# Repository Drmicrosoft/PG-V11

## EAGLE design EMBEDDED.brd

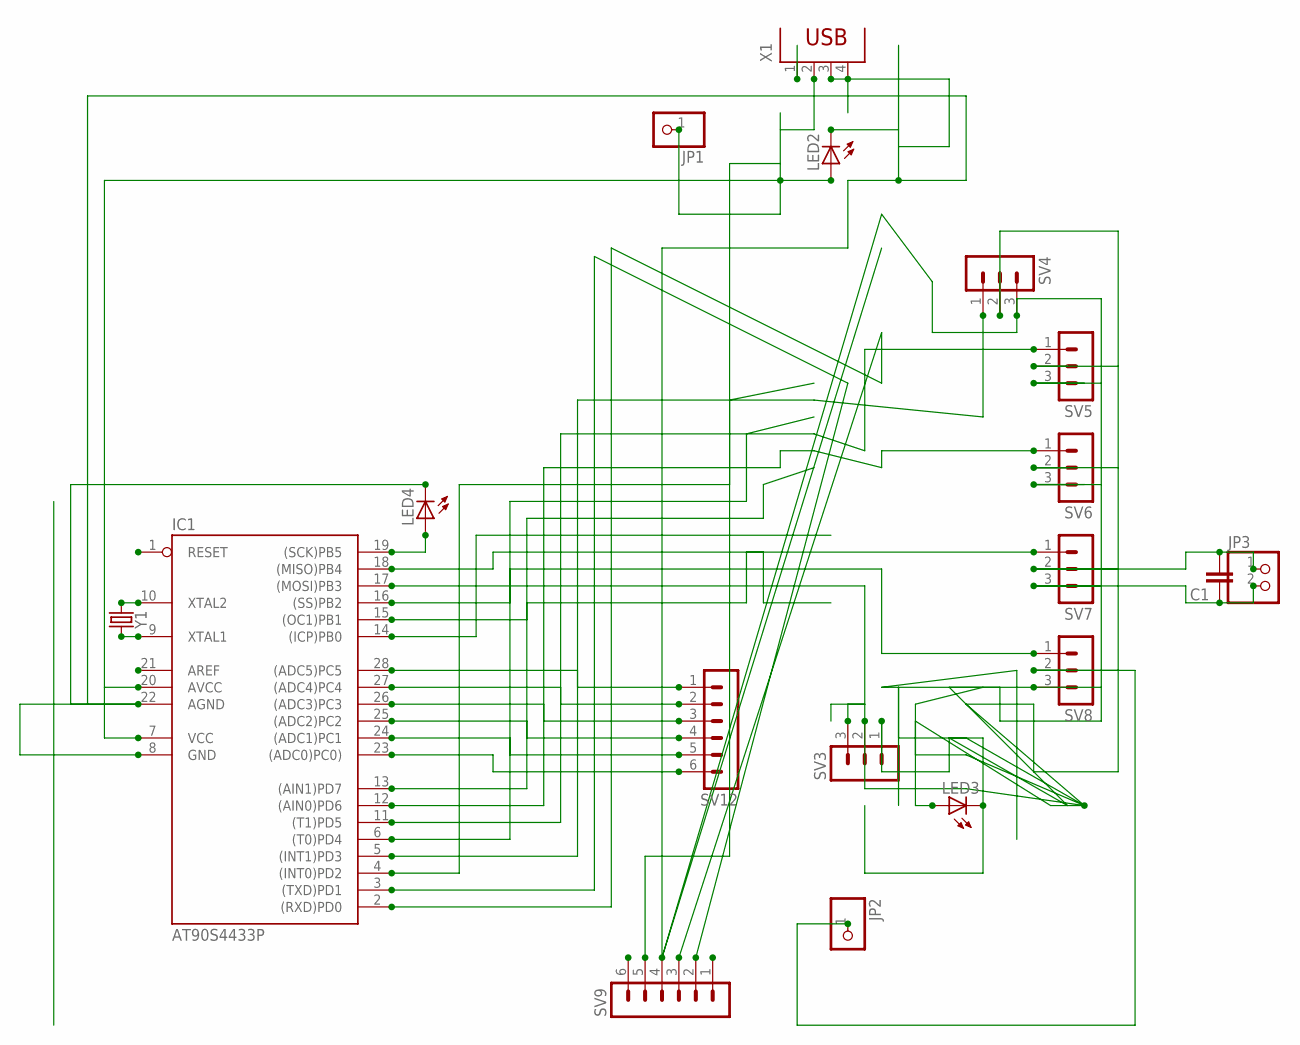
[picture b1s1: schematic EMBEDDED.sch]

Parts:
C1: C5/2.5; C5B2.5
IC1: AT90S4433P; DIL28-3
JP1, JP2: PINHD-1X1; 1X01
JP3: PINHD-1X2; 1X02
LED2, LED3, LED4: LEDLD260; LD260
SV3, SV4, SV5, SV6, SV7, SV8: MA03-1
SV9, SV12: MA06-1
X1: PN61729
Y1: CRYSTALPTH-HC49US; HC49US

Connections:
GROUND: C1.1, IC1.8 (GND), IC1.22 (AGND), JP3.2, LED2.K (C), LED3.K (C), LED4.K (C), SV3.1, SV4.3, SV5.3, SV6.3, SV7.3, SV8.3, SV9.4, X1.3
unnamed: IC1.17 ((MOSI)PB3), SV3.3
unnamed: C1.2, JP2.1, JP3.1, LED3.A, SV3.2, SV4.2, SV5.2, SV6.2, SV7.2, SV8.2
unnamed: IC1.16 ((SS)PB2), SV8.1
unnamed: IC1.15 ((OC1)PB1), SV7.1
unnamed: IC1.12 ((AIN0)PD6), SV6.1
unnamed: IC1.28 ((ADC5)PC5), SV12.1
unnamed: IC1.11 ((T1)PD5), SV5.1
unnamed: IC1.9 (XTAL1), Y1.2
unnamed: IC1.5 ((INT1)PD3), SV4.1
unnamed: IC1.27 ((ADC4)PC4), SV12.2
unnamed: IC1.26 ((ADC3)PC3), SV12.3
unnamed: IC1.2 ((RXD)PD0), SV9.3
unnamed: IC1.3 ((TXD)PD1), SV9.2
unnamed: IC1.25 ((ADC2)PC2), SV12.4
unnamed: IC1.24 ((ADC1)PC1), SV12.5
unnamed: IC1.23 ((ADC0)PC0)), SV12.6
unnamed: IC1.10 (XTAL2), Y1.1
unnamed: IC1.19 ((SCK)PB5), LED4.A
VOLTAGE: IC1.7 (VCC), IC1.20 (AVCC), JP1.1, LED2.A, SV9.5, X1.2

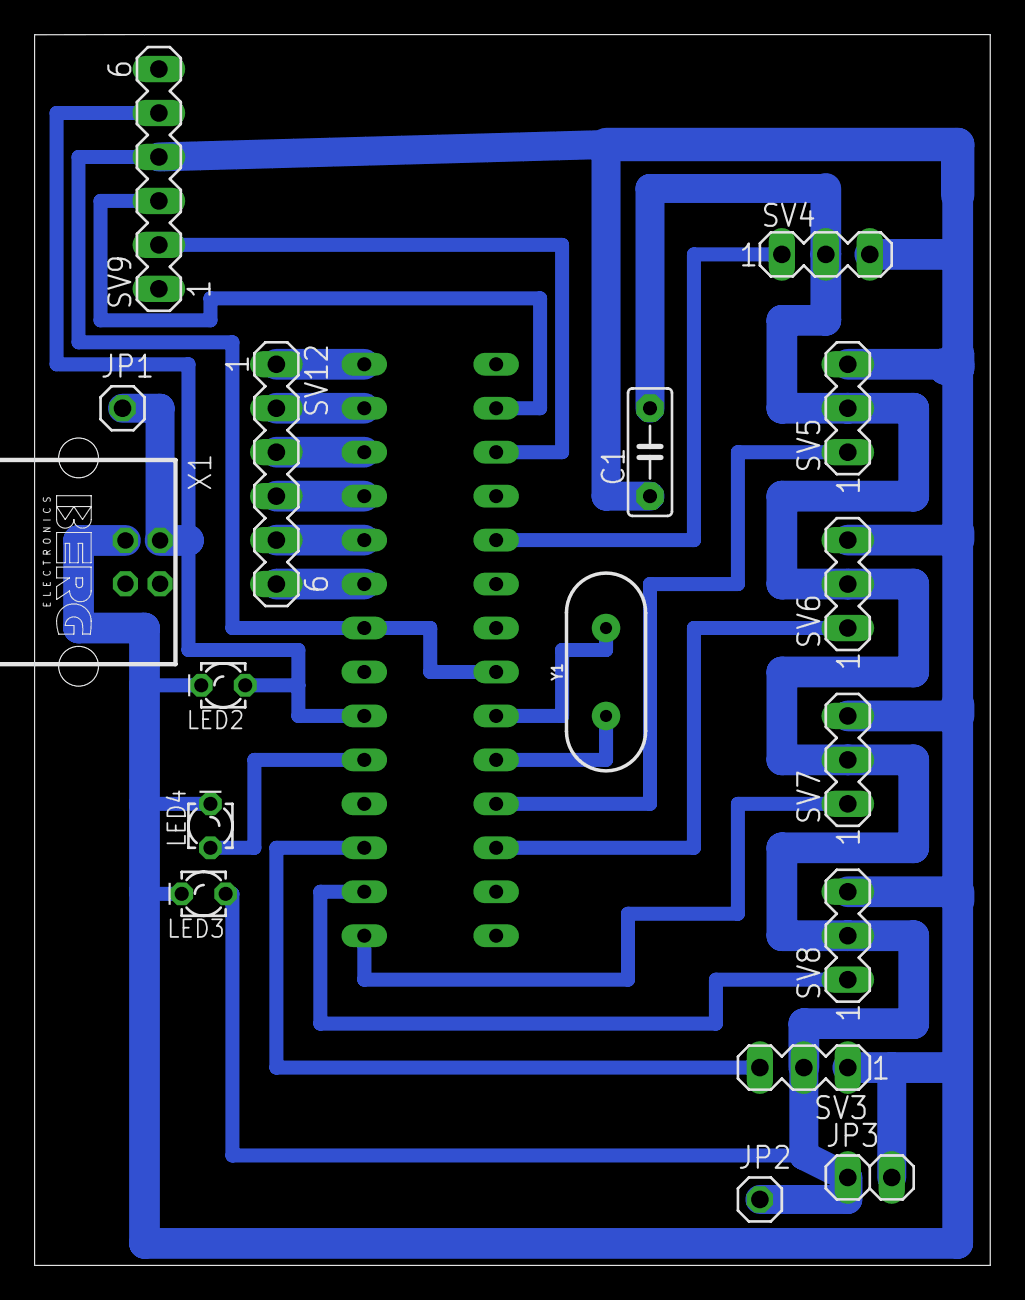
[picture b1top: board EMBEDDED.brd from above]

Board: 2 copper layers, 55.2 x 71.1 mm, 18 parts (1 on the bottom side), 20 nets.

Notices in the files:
parts and their libraries:
SparkFun-Clocks: Licensing: Creative Commons ShareAlike 4.0 International - https://creativecommons.org/licenses/by-sa/4.0
